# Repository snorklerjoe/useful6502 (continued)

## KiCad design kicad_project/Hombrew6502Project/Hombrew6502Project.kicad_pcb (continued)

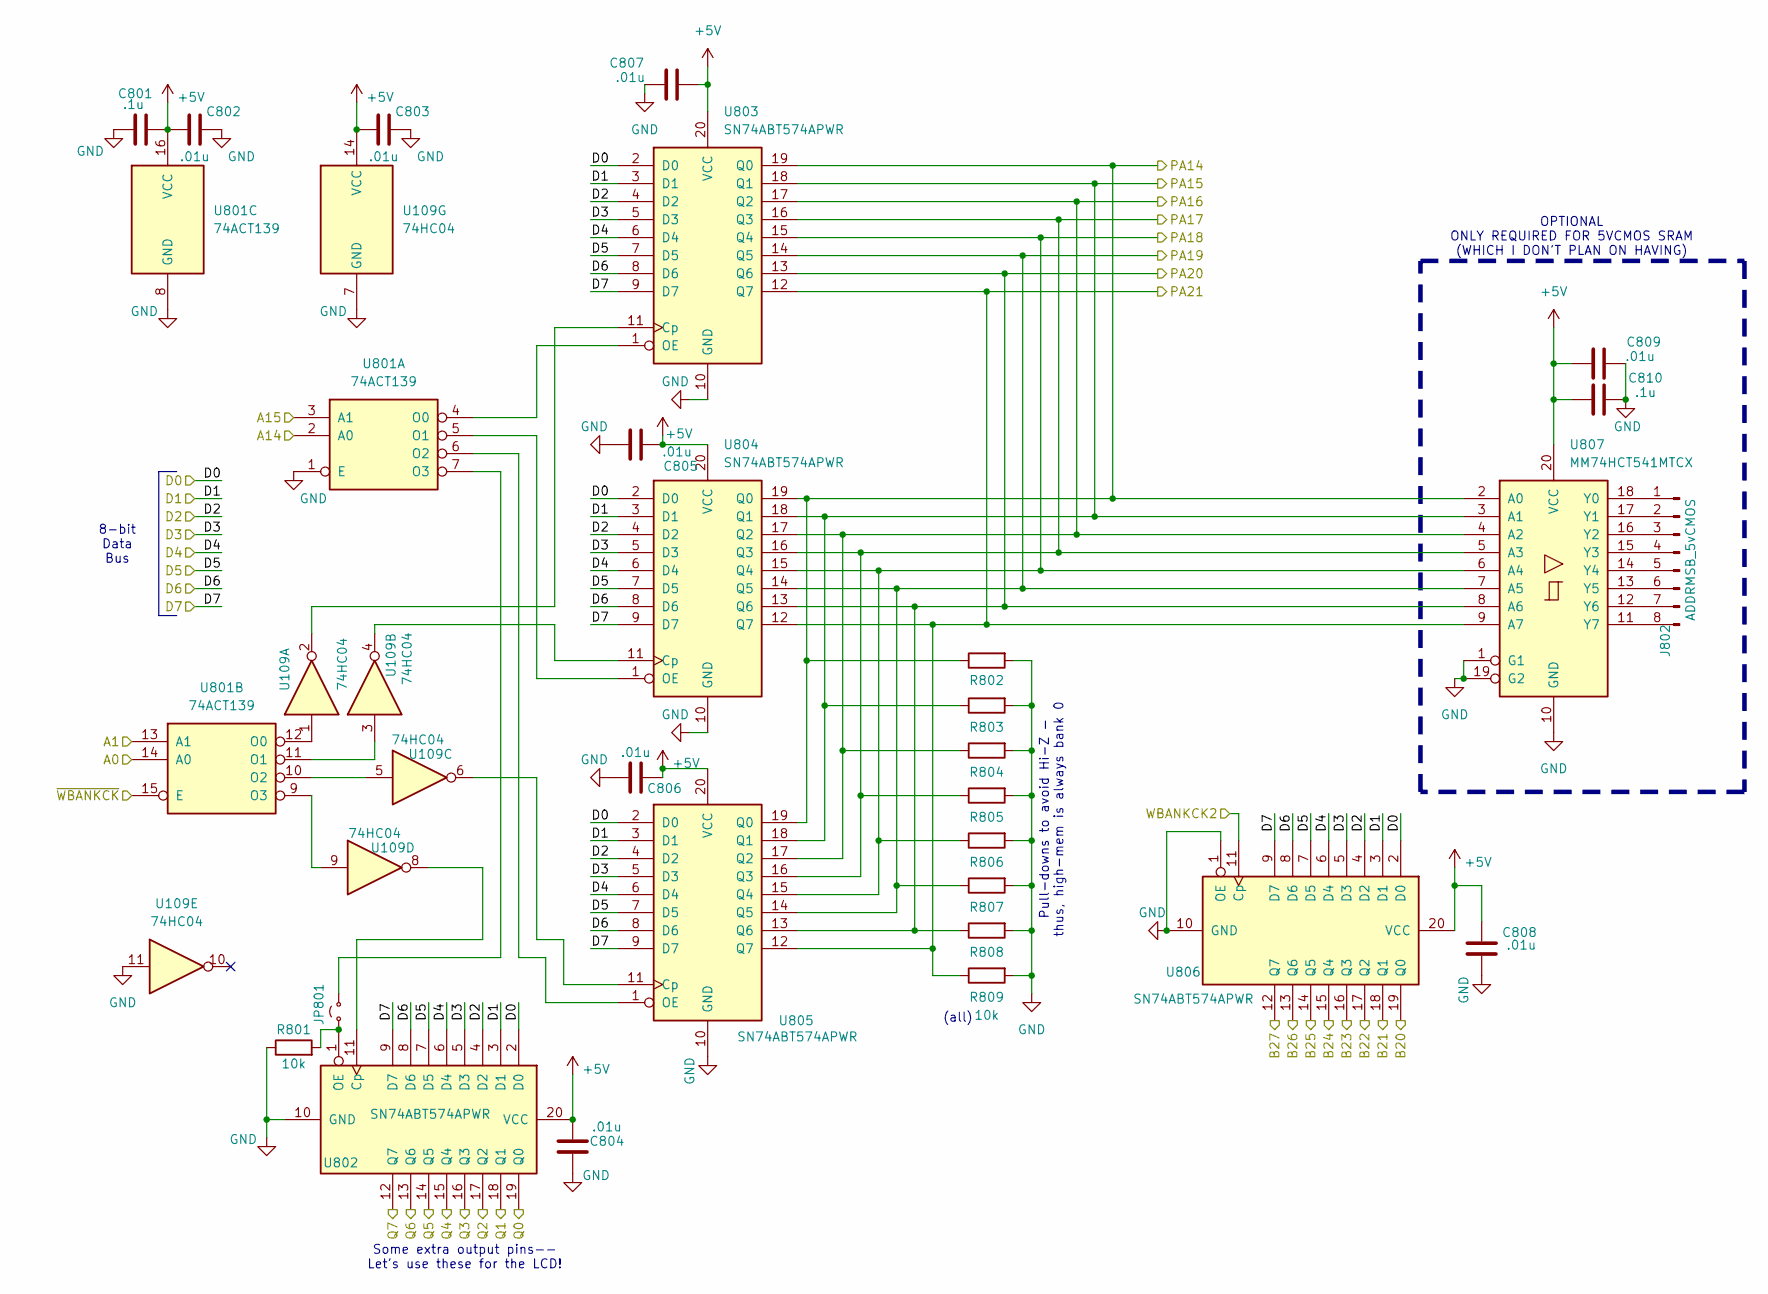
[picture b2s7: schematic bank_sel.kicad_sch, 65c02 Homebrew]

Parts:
C801: .1u; C_0402_1005Metric
C802, C803, C804, C805, C806, C807, C808: .01u; C_0402_1005Metric
C809: .01u
C810: .1u
J802: ADDRMSB_5vCMOS
JP801: Jumper_2_Small_Open; SolderJumper-2_P1.3mm_Open_Pad1.0x1.5mm
R801, R802, R803, R804, R805, R806, R807, R808, R809: 10k; R_0402_1005Metric
U109: 74HC04; SOIC-14_3.9x8.7mm_P1.27mm
U801: 74ACT139; TSSOP-16_4.4x5mm_P0.65mm
U802, U803, U804, U805, U806: SN74ABT574APWR; TSSOP-20_4.4x6.5mm_P0.65mm
U807: MM74HCT541MTCX

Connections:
+5V: C801.2, C802.1, C803.1, C804.2, C805.2, C806.2, C807.1, C808.2, C809.1, C810.1, U109.14 (VCC), U801.16 (VCC), U802.20 (VCC), U803.20 (VCC), U804.20 (VCC), U805.20 (VCC), U806.20 (VCC), U807.20 (VCC); also elsewhere on the board
/A0: U801.14 (A0); also elsewhere on the board
/A1: U801.13 (A1); also elsewhere on the board
/A14: U801.2 (A0); also elsewhere on the board
/A15: U801.3 (A1); also elsewhere on the board
/Bank Selection/WBANKCK2: U806.11 (Cp); also elsewhere on the board
/Bank Selection/~WBANKCK: U801.15 (E); also elsewhere on the board
/D0: U802.2 (D0), U803.2 (D0), U804.2 (D0), U805.2 (D0), U806.2 (D0); also elsewhere on the board
/D1: U802.3 (D1), U803.3 (D1), U804.3 (D1), U805.3 (D1), U806.3 (D1); also elsewhere on the board
/D2: U802.4 (D2), U803.4 (D2), U804.4 (D2), U805.4 (D2), U806.4 (D2); also elsewhere on the board
/D3: U802.5 (D3), U803.5 (D3), U804.5 (D3), U805.5 (D3), U806.5 (D3); also elsewhere on the board
/D4: U802.6 (D4), U803.6 (D4), U804.6 (D4), U805.6 (D4), U806.6 (D4); also elsewhere on the board
/D5: U802.7 (D5), U803.7 (D5), U804.7 (D5), U805.7 (D5), U806.7 (D5); also elsewhere on the board
/D6: U802.8 (D6), U803.8 (D6), U804.8 (D6), U805.8 (D6), U806.8 (D6); also elsewhere on the board
/D7: U802.9 (D7), U803.9 (D7), U804.9 (D7), U805.9 (D7), U806.9 (D7); also elsewhere on the board
/PQ0: U802.19 (Q0); also elsewhere on the board
/PQ1: U802.18 (Q1); also elsewhere on the board
/PQ2: U802.17 (Q2); also elsewhere on the board
/PQ3: U802.16 (Q3); also elsewhere on the board
/PQ4: U802.15 (Q4); also elsewhere on the board
/PQ5: U802.14 (Q5); also elsewhere on the board
/PQ6: U802.13 (Q6); also elsewhere on the board
/PQ7: U802.12 (Q7); also elsewhere on the board
/SRAM Banks/B20: U806.19 (Q0); also elsewhere on the board
/SRAM Banks/B21: U806.18 (Q1); also elsewhere on the board
/SRAM Banks/B22: U806.17 (Q2); also elsewhere on the board
/SRAM Banks/B23: U806.16 (Q3); also elsewhere on the board
/SRAM Banks/B24: U806.15 (Q4); also elsewhere on the board
/SRAM Banks/B25: U806.14 (Q5); also elsewhere on the board
/SRAM Banks/B26: U806.13 (Q6); also elsewhere on the board
/SRAM Banks/B27: U806.12 (Q7); also elsewhere on the board
/SRAM Banks/PA14: R802.1, U803.19 (Q0), U804.19 (Q0), U805.19 (Q0), U807.2 (A0); also elsewhere on the board
/SRAM Banks/PA15: R803.1, U803.18 (Q1), U804.18 (Q1), U805.18 (Q1), U807.3 (A1); also elsewhere on the board
/SRAM Banks/PA16: R804.1, U803.17 (Q2), U804.17 (Q2), U805.17 (Q2), U807.4 (A2); also elsewhere on the board
/SRAM Banks/PA17: R805.1, U803.16 (Q3), U804.16 (Q3), U805.16 (Q3), U807.5 (A3); also elsewhere on the board
/SRAM Banks/PA18: R806.1, U803.15 (Q4), U804.15 (Q4), U805.15 (Q4), U807.6 (A4); also elsewhere on the board
/SRAM Banks/PA19: R807.1, U803.14 (Q5), U804.14 (Q5), U805.14 (Q5), U807.7 (A5); also elsewhere on the board
/SRAM Banks/PA20: R808.1, U803.13 (Q6), U804.13 (Q6), U805.13 (Q6), U807.8 (A6); also elsewhere on the board
/SRAM Banks/PA21: R809.1, U803.12 (Q7), U804.12 (Q7), U805.12 (Q7), U807.9 (A7); also elsewhere on the board
GND: C801.1, C802.2, C803.2, C804.1, C805.1, C806.1, C807.2, C808.1, C809.2, C810.2, R801.1, R802.2, R803.2, R804.2, R805.2, R806.2, R807.2, R808.2, R809.2, U109.7 (GND), U109.11, U801.1 (E), U801.8 (GND), U802.10 (GND), U803.10 (GND), U804.10 (GND), U805.10 (GND), U806.1 (OE), U806.10 (GND), U807.1 (G1), U807.10 (GND), U807.19 (G2); also elsewhere on the board
unnamed: J802.1, U807.18 (Y0)
unnamed: J802.2, U807.17 (Y1)
unnamed: J802.3, U807.16 (Y2)
unnamed: J802.4, U807.15 (Y3)
unnamed: J802.5, U807.14 (Y4)
unnamed: J802.6, U807.13 (Y5)
unnamed: J802.7, U807.12 (Y6)
unnamed: J802.8, U807.11 (Y7)
unnamed: JP801.1 (A), R801.2, U802.1 (OE)
unnamed: JP801.2 (B), U801.7 (O3)
unnamed: U801.4 (O0), U803.1 (OE)
unnamed: U801.5 (O1), U804.1 (OE)
unnamed: U801.6 (O2), U805.1 (OE)
unnamed: U109.1, U801.12 (O0)
unnamed: U109.3, U801.11 (O1)
unnamed: U109.5, U801.10 (O2)
unnamed: U109.9, U801.9 (O3)
unnamed: U109.8, U802.11 (Cp)
unnamed: U109.2, U803.11 (Cp)
unnamed: U109.4, U804.11 (Cp)
unnamed: U109.6, U805.11 (Cp)

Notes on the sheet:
Pull-downs to avoid Hi-Z — thus, high-mem is always bank 0
8-bit Data Bus
OPTIONAL ONLY REQUIRED FOR 5VCMOS SRAM (WHICH I DON'T PLAN ON HAVING)
Some extra output pins-- Let's use these for the LCD!
(all)

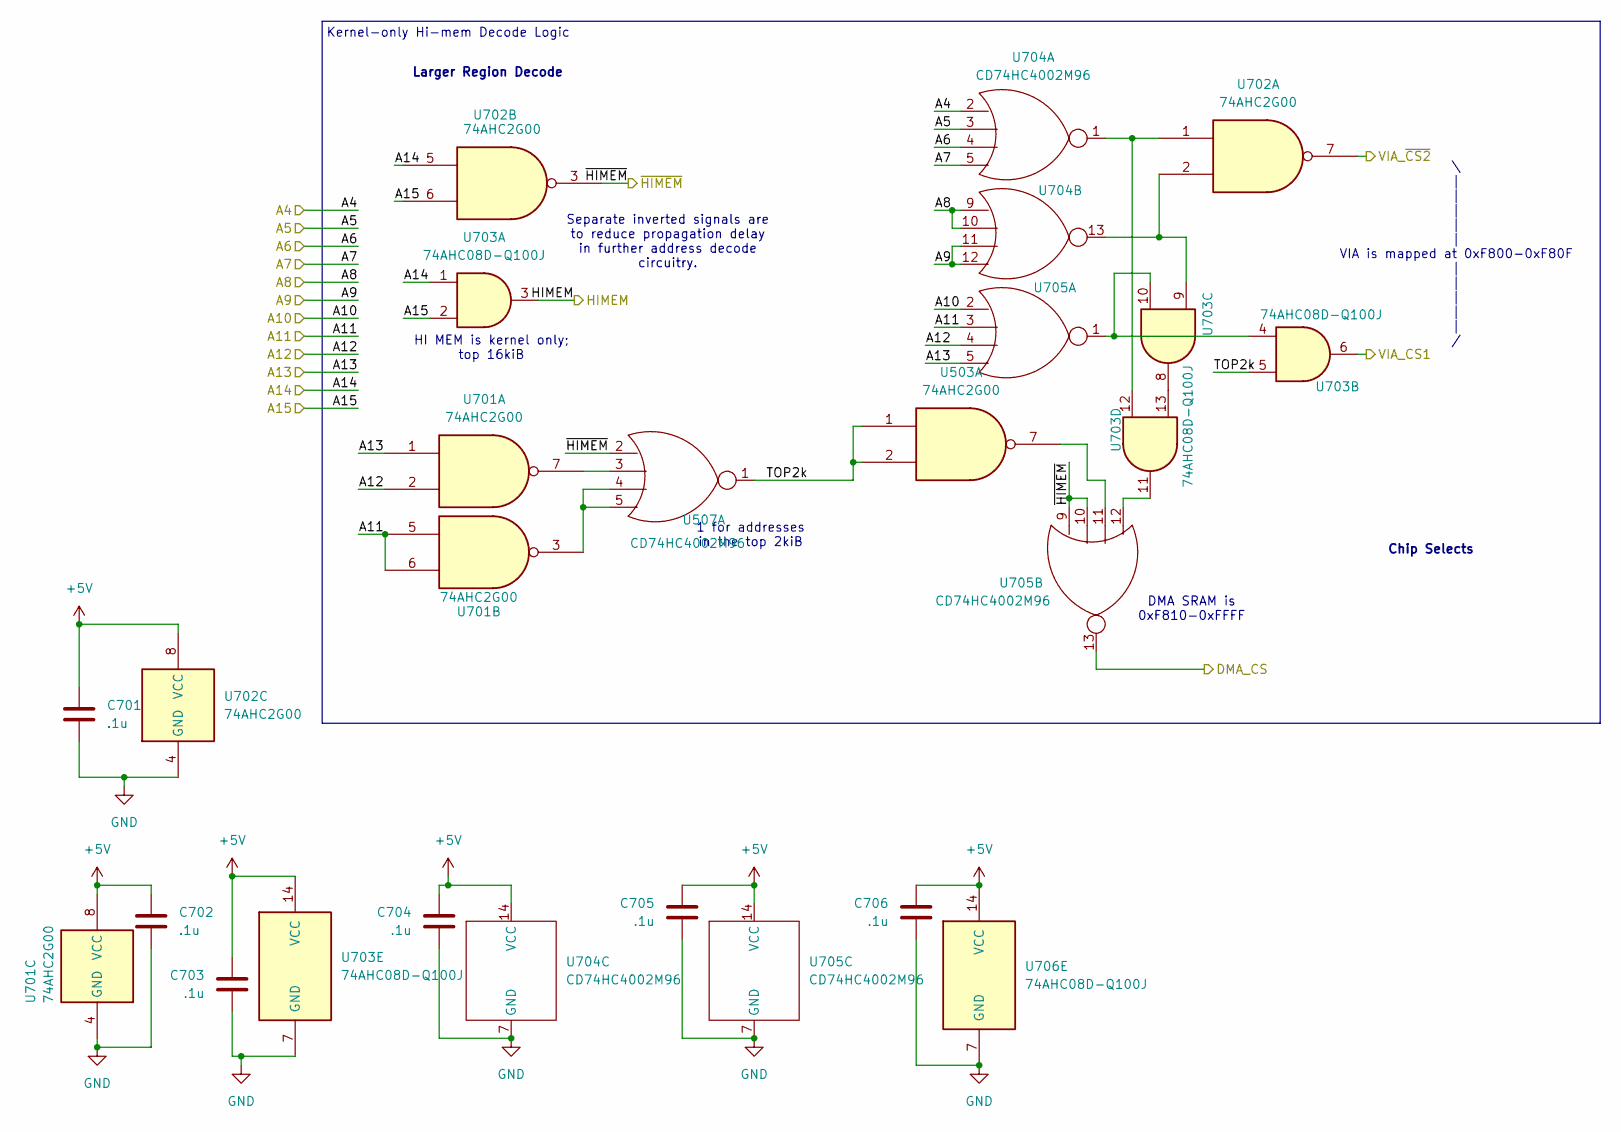
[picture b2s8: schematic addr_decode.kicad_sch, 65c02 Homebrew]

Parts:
C701, C702, C703, C704, C705, C706: .1u; C_0402_1005Metric
U503, U701, U702: 74AHC2G00; TSSOP-8_3x3mm_P0.65mm
U507, U704, U705: CD74HC4002M96; SOIC-14_3.9x8.7mm_P1.27mm
U703, U706: 74AHC08D-Q100J; SOIC-14_3.9x8.7mm_P1.27mm

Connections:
+5V: C701.1, C702.1, C703.1, C704.1, C705.1, C706.1, U701.8 (VCC), U702.8 (VCC), U703.14 (VCC), U704.14 (VCC), U705.14 (VCC), U706.14 (VCC); also elsewhere on the board
/A4: U704.2; also elsewhere on the board
/A5: U704.3; also elsewhere on the board
/A6: U704.4; also elsewhere on the board
/A7: U704.5; also elsewhere on the board
/A8: U704.9, U704.10; also elsewhere on the board
/A9: U704.11, U704.12; also elsewhere on the board
/A10: U705.2; also elsewhere on the board
/A11: U701.5, U701.6, U705.3; also elsewhere on the board
/A12: U701.2, U705.4; also elsewhere on the board
/A13: U701.1, U705.5; also elsewhere on the board
/A14: U702.5, U703.1; also elsewhere on the board
/A15: U702.6, U703.2; also elsewhere on the board
/HIMEM: U703.3; also elsewhere on the board
/High-Memory Address Decode/TOP2k: U503.1, U503.2, U507.1, U703.5
/VIA_CS1: U703.6; also elsewhere on the board
/VIA_~CS2: U702.7; also elsewhere on the board
/~DMA_CS: U705.13; also elsewhere on the board
/~HIMEM: U507.2, U702.3, U705.9, U705.10; also elsewhere on the board
GND: C701.2, C702.2, C703.2, C704.2, C705.2, C706.2, U701.4 (GND), U702.4 (GND), U703.7 (GND), U704.7 (GND), U705.7 (GND), U706.7 (GND); also elsewhere on the board
unnamed: U503.7, U705.11
unnamed: U507.3, U701.7
unnamed: U507.4, U507.5, U701.3
unnamed: U702.1, U703.12, U704.1
unnamed: U702.2, U703.9, U704.13
unnamed: U703.4, U703.10, U705.1
unnamed: U703.11, U705.12
unnamed: U703.8, U703.13

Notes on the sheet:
Larger Region Decode
Separate inverted signals are to reduce propagation delay in further address decode circuitry.
HI MEM is kernel only; top 16kiB
Chip Selects
Kernel-only Hi-mem Decode Logic
\ | | | | | VIA is mapped at 0xF800-0xF80F | | | | | /
1 for addresses in the top 2kiB
DMA SRAM is 0xF810-0xFFFF

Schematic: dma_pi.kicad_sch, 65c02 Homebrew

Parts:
C201: 4.7u; C_0402_1005Metric
C202, C209, C213, C216, C217: .01u; C_0402_1005Metric
C203, C204: NOPOP; C_0402_1005Metric
C205: .01u; C_0402_1005Metric; not fitted
C206, C211: 0.1u; C_0402_1005Metric
C207, C210, C212, C214: 1u; C_0402_1005Metric
C208, C215, C218: .1u; C_0402_1005Metric
J201: ICSP Header; PinHeader_1x06_P2.54mm_Vertical
J202, J203, J205, J206: Conn_02x05_Odd_Even; PinHeader_2x05_P2.54mm_Vertical_SMD
J204: I2C; PinHeader_1x05_P2.54mm_Vertical
J210: UART; FanPinHeader_1x03_P2.54mm_Vertical
JP201: Jumper_2_Small_Bridged; SolderJumper-2_P1.3mm_Bridged2Bar_Pad1.0x1.5mm
JP202: Jumper_2_Small_Open; SolderJumper-2_P1.3mm_Open_Pad1.0x1.5mm
JP203: ICSP modeset; SolderJumper-2_P1.3mm_Bridged2Bar_Pad1.0x1.5mm
JP204: BS_CTRL; SolderJumper-2_P1.3mm_Open_Pad1.0x1.5mm
JP205: BS_CTRL2; SolderJumper-2_P1.3mm_Bridged2Bar_Pad1.0x1.5mm
JP206: OE_CTRL; SolderJumper-2_P1.3mm_Bridged2Bar_Pad1.0x1.5mm
JP207: RW_CTRL; SolderJumper-2_P1.3mm_Bridged2Bar_Pad1.0x1.5mm
JP208: CE_CTRL; SolderJumper-2_P1.3mm_Open_Pad1.0x1.5mm
JP209: UART pin sel; SolderJumper-3_P1.3mm_Bridged12_Pad1.0x1.5mm
R201: NOPOP; R_0402_1005Metric
R202, R203: NOPOP; R_0402_1005Metric; not fitted
R204, R215, R219, R220, R221: 4.7k; R_0402_1005Metric
R205, R206, R207, R208, R209, R210, R211, R212: 33; R_0402_1005Metric
R213, R214, R218: 100; R_0402_1005Metric
R216, R217: 10k; R_0402_1005Metric
TP201: INT; TestPoint_Pad_D1.5mm
U201: SN74LS07; SOIC-14_3.9x8.7mm_P1.27mm
U202: CY7C146-25JC; 845221B1RKTP
U203: PIC16F15385-xPT; TQFP-48_7x7mm_P0.5mm
Y201: NOPOP; Crystal_SMD_2016-4Pin_2.0x1.6mm

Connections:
+3V3: J203.6, J204.1, J205.6; also elsewhere on the board
+5V: C201.1, C202.2, C205.2, C206.1, C207.1, C208.1, C209.1, C210.1, C211.1, C212.1, C214.1, C215.1, C216.1, C217.1, C218.1, J201.2, J202.3, J203.4, J204.2, J205.4, J206.10, R202.2, R203.2, R216.1, R217.1, U201.14 (VCC), U202.52 (VCC), U203.7 (VDD), U203.30 (VDD); also elsewhere on the board
/A0: U202.7 (A0_L); also elsewhere on the board
/A1: U202.8 (A1_L); also elsewhere on the board
/A2: U202.9 (A2_L); also elsewhere on the board
/A3: U202.10 (A3_L); also elsewhere on the board
/A4: U202.11 (A4_L); also elsewhere on the board
/A5: U202.12 (A5_L); also elsewhere on the board
/A6: U202.13 (A6_L); also elsewhere on the board
/A7: U202.14 (A7_L); also elsewhere on the board
/A8: U202.15 (A8_L); also elsewhere on the board
/A9: U202.16 (A9_L); also elsewhere on the board
/A10: U202.5 (A10_L); also elsewhere on the board
/DMA Peripheral Interface/6502_D0: R205.1; also elsewhere on the board
/DMA Peripheral Interface/6502_D1: R206.1; also elsewhere on the board
/DMA Peripheral Interface/6502_D2: R207.1; also elsewhere on the board
/DMA Peripheral Interface/6502_D3: R208.1; also elsewhere on the board
/DMA Peripheral Interface/6502_D4: R209.1; also elsewhere on the board
/DMA Peripheral Interface/6502_D5: R210.1; also elsewhere on the board
/DMA Peripheral Interface/6502_D6: R211.1; also elsewhere on the board
/DMA Peripheral Interface/6502_D7: R212.1; also elsewhere on the board
/DMA Peripheral Interface/DMA Peripheral Interface Module/AUX_INT1: J206.6, U201.3
/DMA Peripheral Interface/DMA Peripheral Interface Module/AUX_SEL: J202.10, J206.4, JP204.2 (B), U203.2 (RD4)
/DMA Peripheral Interface/DMA Peripheral Interface Module/CLKIN: C204.1, U203.32 (RA7), Y201.1
/DMA Peripheral Interface/DMA Peripheral Interface Module/CLKOUT: R201.1, U203.33 (RA6)
/DMA Peripheral Interface/DMA Peripheral Interface Module/DMA_A0: U202.45 (A0_R), U203.34 (RC0)
/DMA Peripheral Interface/DMA Peripheral Interface Module/DMA_A1: U202.44 (A1_R), U203.35 (RC1)
/DMA Peripheral Interface/DMA Peripheral Interface Module/DMA_A2: U202.43 (A2_R), U203.40 (RC2)
/DMA Peripheral Interface/DMA Peripheral Interface Module/DMA_A3: U202.42 (A3_R), U203.41 (RC3)
/DMA Peripheral Interface/DMA Peripheral Interface Module/DMA_A4: U202.41 (A4_R), U203.46 (RC4)
/DMA Peripheral Interface/DMA Peripheral Interface Module/DMA_A5: U202.40 (A5_R), U203.47 (RC5)
/DMA Peripheral Interface/DMA Peripheral Interface Module/DMA_A6: U202.39 (A6_R), U203.48 (RC6)
/DMA Peripheral Interface/DMA Peripheral Interface Module/DMA_A7: U202.38 (A7_R), U203.1 (RC7)
/DMA Peripheral Interface/DMA Peripheral Interface Module/DMA_A8: U202.37 (A8_R), U203.29 (RE2)
/DMA Peripheral Interface/DMA Peripheral Interface Module/DMA_A9: U202.36 (A9_R), U203.28 (RE1)
/DMA Peripheral Interface/DMA Peripheral Interface Module/DMA_A10: U202.47 (A10_R), U203.27 (RE0)
/DMA Peripheral Interface/DMA Peripheral Interface Module/DMA_BS: JP204.1 (A), JP205.1 (A), U202.49 (BUSY_R)
/DMA Peripheral Interface/DMA Peripheral Interface Module/DMA_CE: JP208.2 (B), R215.2, U202.51 (CE_R)
/DMA Peripheral Interface/DMA Peripheral Interface Module/DMA_D0: U202.27 (D0_R), U203.36 (RF0)
/DMA Peripheral Interface/DMA Peripheral Interface Module/DMA_D1: U202.28 (D1_R), U203.37 (RF1)
/DMA Peripheral Interface/DMA Peripheral Interface Module/DMA_D2: U202.29 (D2_R), U203.38 (RF2)
/DMA Peripheral Interface/DMA Peripheral Interface Module/DMA_D3: U202.30 (D3_R), U203.39 (RF3)
/DMA Peripheral Interface/DMA Peripheral Interface Module/DMA_D4: U202.31 (D4_R), U203.12 (RF4)
/DMA Peripheral Interface/DMA Peripheral Interface Module/DMA_D5: U202.32 (D5_R), U203.13 (RF5)
/DMA Peripheral Interface/DMA Peripheral Interface Module/DMA_D6: U202.33 (D6_R), U203.14 (RF6)
/DMA Peripheral Interface/DMA Peripheral Interface Module/DMA_D7: U202.34 (D7_R), U203.15 (RF7)
/DMA Peripheral Interface/DMA Peripheral Interface Module/DMA_INT: R216.2, U202.48 (INT_R)
/DMA Peripheral Interface/DMA Peripheral Interface Module/DMA_OE: JP206.2 (B), U202.46 (OE_R)
/DMA Peripheral Interface/DMA Peripheral Interface Module/DMA_RW: JP207.2 (B), U202.50 (RW_R)
/DMA Peripheral Interface/DMA Peripheral Interface Module/PIC Peripherals/OC_MO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: U201.10; also elsewhere on the board
/DMA Peripheral Interface/DMA Peripheral Interface Module/PIC Peripherals/OC_SCK: U201.12; also elsewhere on the board
/DMA Peripheral Interface/DMA Peripheral Interface Module/PIC Peripherals/OC_SS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: U201.8; also elsewhere on the board
/DMA Peripheral Interface/DMA Peripheral Interface Module/PIC_INT: U201.2, U201.4, U203.26 (RA5)
/DMA Peripheral Interface/DMA Peripheral Interface Module/SS_AUX: J206.9, U203.23 (RA2)
/DMA Peripheral Interface/DMA Peripheral Interface Module/SS_MEM: U203.25 (RA4); also elsewhere on the board
/DMA Peripheral Interface/DMA Peripheral Interface Module/SS_SD: U201.9, U203.24 (RA3)
/DMA Peripheral Interface/DMA Peripheral Interface Module/UARTrx: J203.9, J205.9, J210.2, R220.2
/DMA Peripheral Interface/DMA Peripheral Interface Module/UARTtx: J203.7, J205.7, J210.3, R219.1
/DMA Peripheral Interface/~BUSY: U202.3 (BUSY_L); also elsewhere on the board
/IO_CMD: U201.1; also elsewhere on the board
/R~W: U202.2 (RW_L); also elsewhere on the board
/~DMA_CS: JP201.2 (B), JP202.1 (A); also elsewhere on the board
/~IRQ: U203.21 (RA0); also elsewhere on the board
GND: C201.2, C202.1, C203.1, C204.2, C205.1, C206.2, C207.2, C208.2, C209.2, C210.2, C211.2, C212.2, C213.2, C214.2, C215.2, C216.2, C217.2, C218.2, J201.3, J202.1, J203.2, J203.5, J203.8, J203.10, J204.5, J205.2, J205.5, J205.8, J205.10, J206.2, J206.7, J206.8, J210.1, R204.2, R215.1, R221.2, U201.7 (GND), U202.26 (GND), U203.6 (VSS), U203.31 (VSS), Y201.2, Y201.4; also elsewhere on the board
ICSPCLK: JP209.3 (B), R214.1, U203.18 (ICSPCLK/RB6)
ICSPDAT: JP209.1 (A), R213.1, U203.19 (ICSPDAT/RB7)
ICSPMCLR: J201.1, JP203.2 (B), R217.2, R218.1
MISO: J206.5, U203.9 (RB1); also elsewhere on the board
MOSI: J206.3, U201.11, U203.10 (RB2); also elsewhere on the board
unnamed: C203.2, R201.2, Y201.3
unnamed: J201.4, R213.2
unnamed: J201.5, R214.2
unnamed: J202.2, U203.42 (RD0)
unnamed: J202.4, U203.43 (RD1)
unnamed: J202.5, JP206.1 (A), U203.5 (RD7)
unnamed: J202.6, U203.44 (RD2)
unnamed: J202.7, JP207.1 (A), U203.4 (RD6)
unnamed: J202.8, U203.45 (RD3)
unnamed: J202.9, JP205.2 (B), JP208.1 (A), U203.3 (RD5)
unnamed: JP201.1 (A), U202.6 (OE_L)
unnamed: JP202.2 (B), R204.1, U202.1 (CE_L)
unnamed: C213.1, JP203.1 (A)
unnamed: JP209.2 (C), R220.1
unnamed: R205.2, U202.17 (D0_L)
unnamed: R206.2, U202.18 (D1_L)
unnamed: R207.2, U202.19 (D2_L)
unnamed: R208.2, U202.20 (D3_L)
unnamed: R209.2, U202.21 (D4_L)
unnamed: R210.2, U202.22 (D5_L)
unnamed: R211.2, U202.23 (D6_L)
unnamed: R212.2, U202.24 (D7_L)
unnamed: TP201.1, U202.4 (INT_L)
unnamed: R221.1, U201.5, U203.22 (RA1)
unnamed: R219.2, U203.17 (RB5)
unnamed: R218.2, U203.20 (VPP/~MCLR/RE3)
RESB: U201.6; also elsewhere on the board
SCK: J206.1, U201.13, U203.8 (RB0); also elsewhere on the board
SCL: J203.3, J204.4, J205.3, R203.1, U203.11 (RB3)
SDA: J203.1, J204.3, J205.1, R202.1, U203.16 (RB4)

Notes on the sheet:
Peripherals
PIC AUX Interfaces
SPI Slave Select
Interrupt line to 6502 for DMA data ready (CMOS compatible)
DMA Interrupt Lines (Active Low)
(for ext. crystal)
(PIC16 Peripheral Interface Coprocessor)
Optional external i2c pull-ups These can be internal to the PIC. Otherwise, these should both be ≥4.7k
Optional PIC Interfaces
Provision for an external ESP-01 Interface
Optional external crystal; enable in software if provided
Interrupt line to PIC for DMA data ready (CMOS-compatible)
Dual-port RAM is used as hardware-shared memory between 6502 & PIC
ICSP & UART
SPI Master
To reset the CPU
I2C Master
Resistors in case of accidentally reversing tx & rx

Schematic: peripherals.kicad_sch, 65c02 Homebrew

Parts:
C401, C403: 1u; C_0402_1005Metric
C402, C404: .1u; C_0402_1005Metric
C405: .01u; C_0402_1005Metric
D401: LED; LED_0402_1005Metric
J402: Micro_SD_Card; microSD_HC_Wuerth_693072010801
J403: Conn_02x03_Odd_Even; PinHeader_2x03_P2.54mm_Vertical_SMD
R401, R402, R403, R404: 10k; R_0402_1005Metric
R405: 470; R_0402_1005Metric
U401: 74HCT125D; SOIC-14_3.9x8.7mm_P1.27mm
U402: M95512-Axxx-MF; TSSOP-8_4.4x3mm_P0.65mm

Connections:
+3V3: C403.1, C404.1, J402.4 (VDD), J403.5, R401.1, R402.1, R403.1, R404.1, R405.2; also elsewhere on the board
+5V: C401.1, C402.1, C405.1, U401.14 (Vcc), U402.3 (~W), U402.7 (~HOLD), U402.8 (VCC); also elsewhere on the board
/DMA Peripheral Interface/DMA Peripheral Interface Module/PIC Peripherals/OC_MO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: J402.3 (CMD), J403.3, R402.2; also elsewhere on the board
/DMA Peripheral Interface/DMA Peripheral Interface Module/PIC Peripherals/OC_SCK: J402.5 (CLK), J403.6, R403.2; also elsewhere on the board
/DMA Peripheral Interface/DMA Peripheral Interface Module/PIC Peripherals/OC_SS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: D401.1 (K), J402.2 (DAT3/CD), J403.1, R404.2, U401.1 (~OE); also elsewhere on the board
/DMA Peripheral Interface/DMA Peripheral Interface Module/PIC Peripherals/SD_MI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: J402.7 (DAT0), J403.2, R401.2, U401.2 (A)
/DMA Peripheral Interface/DMA Peripheral Interface Module/SS_MEM: U402.1 (~S); also elsewhere on the board
GND: C401.2, C402.2, C403.2, C404.2, C405.2, J402.6 (VSS), J402.9 (SHIELD), J403.4, U401.4 (~OE), U401.5 (A), U401.7 (GND), U401.9 (A), U401.10 (~OE), U401.12 (A), U401.13 (~OE), U402.4 (VSS); also elsewhere on the board
MISO: U401.3 (Y), U402.2 (Q); also elsewhere on the board
MOSI: U402.5 (D); also elsewhere on the board
unnamed: D401.2 (A), R405.1
SCK: U402.6 (C); also elsewhere on the board

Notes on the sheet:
3.3v CMOS (5V TTL-compatible)
Interface from DMA Schematic
Unused Components
EEPROM Slave Select
SD Card Hardware
\ | SPI | /
Pull-ups for open- collector
SPI EEPROM (for 6502 boot image)
Tri-state 5V CMOS
Optional, Provisionary Interfaces
Open-collector SD SPI signals
SD Card BUSY

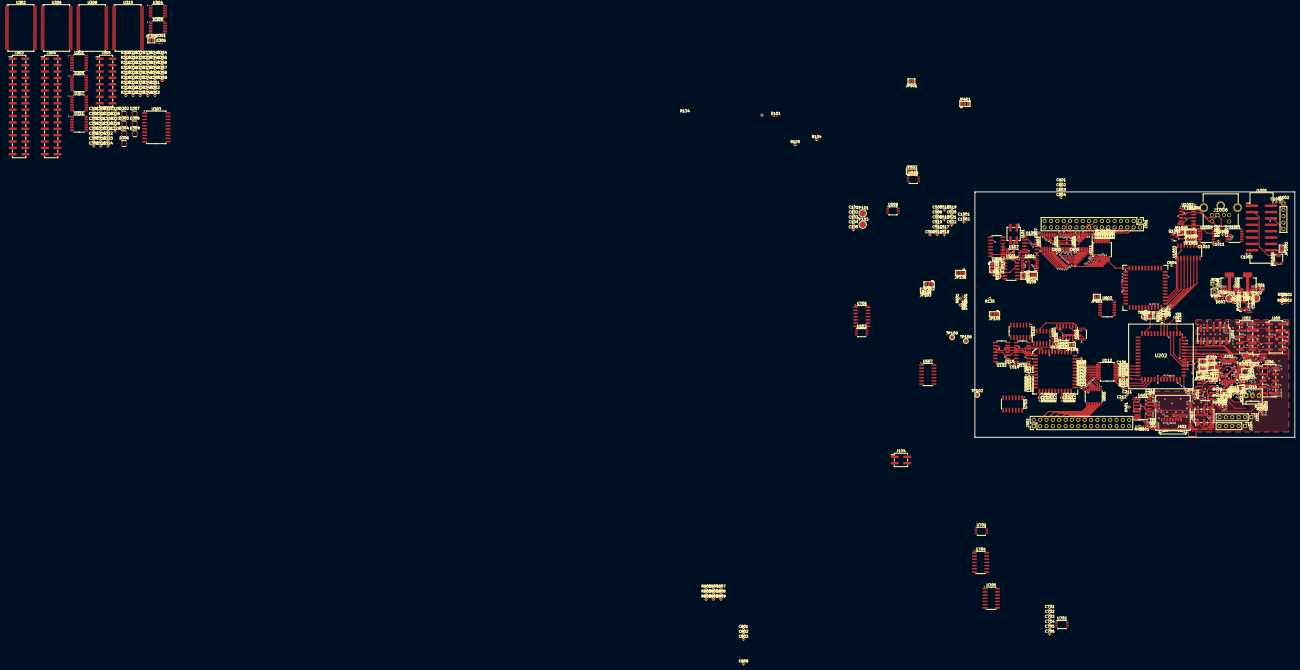
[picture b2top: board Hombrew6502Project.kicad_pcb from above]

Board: 4 copper layers, 127.6 x 98.0 mm, 378 parts (0 on the bottom side), 408 nets.

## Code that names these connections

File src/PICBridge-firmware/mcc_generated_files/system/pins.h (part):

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// get/set IO_RA5 aliases
#define IO_RA5_TRIS                 TRISAbits.TRISA5
#define IO_RA5_LAT                  LATAbits.LATA5
#define IO_RA5_PORT                 PORTAbits.RA5
#define IO_RA5_WPU                  WPUAbits.WPUA5
#define IO_RA5_OD                   ODCONAbits.ODCA5
#define IO_RA5_ANS                  ANSELAbits.ANSA5
#define IO_RA5_SetHigh()            do { LATAbits.LATA5 = 1; } while(0)
#define IO_RA5_SetLow()             do { LATAbits.LATA5 = 0; } while(0)
#define IO_RA5_Toggle()             do { LATAbits.LATA5 = ~LATAbits.LATA5; } while(0)
#define IO_RA5_GetValue()           PORTAbits.RA5
#define IO_RA5_SetDigitalInput()    do { TRISAbits.TRISA5 = 1; } while(0)
#define IO_RA5_SetDigitalOutput()   do { TRISAbits.TRISA5 = 0; } while(0)
#define IO_RA5_SetPullup()          do { WPUAbits.WPUA5 = 1; } while(0)
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// get/set IO_RB0 aliases
#define IO_RB0_TRIS                 TRISBbits.TRISB0
#define IO_RB0_LAT                  LATBbits.LATB0
#define IO_RB0_PORT                 PORTBbits.RB0
#define IO_RB0_WPU                  WPUBbits.WPUB0
#define IO_RB0_OD                   ODCONBbits.ODCB0
#define IO_RB0_ANS                  ANSELBbits.ANSB0
#define IO_RB0_SetHigh()            do { LATBbits.LATB0 = 1; } while(0)
#define IO_RB0_SetLow()             do { LATBbits.LATB0 = 0; } while(0)
#define IO_RB0_Toggle()             do { LATBbits.LATB0 = ~LATBbits.LATB0; } while(0)
#define IO_RB0_GetValue()           PORTBbits.RB0
#define IO_RB0_SetDigitalInput()    do { TRISBbits.TRISB0 = 1; } while(0)
#define IO_RB0_SetDigitalOutput()   do { TRISBbits.TRISB0 = 0; } while(0)
#define IO_RB0_SetPullup()          do { WPUBbits.WPUB0 = 1; } while(0)
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// get/set IO_RB1 aliases
#define IO_RB1_TRIS                 TRISBbits.TRISB1
#define IO_RB1_LAT                  LATBbits.LATB1
#define IO_RB1_PORT                 PORTBbits.RB1
#define IO_RB1_WPU                  WPUBbits.WPUB1
#define IO_RB1_OD                   ODCONBbits.ODCB1
#define IO_RB1_ANS                  ANSELBbits.ANSB1
#define IO_RB1_SetHigh()            do { LATBbits.LATB1 = 1; } while(0)
#define IO_RB1_SetLow()             do { LATBbits.LATB1 = 0; } while(0)
#define IO_RB1_Toggle()             do { LATBbits.LATB1 = ~LATBbits.LATB1; } while(0)
#define IO_RB1_GetValue()           PORTBbits.RB1
#define IO_RB1_SetDigitalInput()    do { TRISBbits.TRISB1 = 1; } while(0)
#define IO_RB1_SetDigitalOutput()   do { TRISBbits.TRISB1 = 0; } while(0)
#define IO_RB1_SetPullup()          do { WPUBbits.WPUB1 = 1; } while(0)
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// get/set IO_RB2 aliases
#define IO_RB2_TRIS                 TRISBbits.TRISB2
#define IO_RB2_LAT                  LATBbits.LATB2
#define IO_RB2_PORT                 PORTBbits.RB2
#define IO_RB2_WPU                  WPUBbits.WPUB2
#define IO_RB2_OD                   ODCONBbits.ODCB2
#define IO_RB2_ANS                  ANSELBbits.ANSB2
#define IO_RB2_SetHigh()            do { LATBbits.LATB2 = 1; } while(0)
#define IO_RB2_SetLow()             do { LATBbits.LATB2 = 0; } while(0)
#define IO_RB2_Toggle()             do { LATBbits.LATB2 = ~LATBbits.LATB2; } while(0)
#define IO_RB2_GetValue()           PORTBbits.RB2
#define IO_RB2_SetDigitalInput()    do { TRISBbits.TRISB2 = 1; } while(0)
#define IO_RB2_SetDigitalOutput()   do { TRISBbits.TRISB2 = 0; } while(0)
#define IO_RB2_SetPullup()          do { WPUBbits.WPUB2 = 1; } while(0)
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// get/set IO_RB3 aliases
#define IO_RB3_TRIS                 TRISBbits.TRISB3
#define IO_RB3_LAT                  LATBbits.LATB3
#define IO_RB3_PORT                 PORTBbits.RB3
#define IO_RB3_WPU                  WPUBbits.WPUB3
#define IO_RB3_OD                   ODCONBbits.ODCB3
#define IO_RB3_ANS                  ANSELBbits.ANSB3
#define IO_RB3_SetHigh()            do { LATBbits.LATB3 = 1; } while(0)
#define IO_RB3_SetLow()             do { LATBbits.LATB3 = 0; } while(0)
#define IO_RB3_Toggle()             do { LATBbits.LATB3 = ~LATBbits.LATB3; } while(0)
#define IO_RB3_GetValue()           PORTBbits.RB3
#define IO_RB3_SetDigitalInput()    do { TRISBbits.TRISB3 = 1; } while(0)
#define IO_RB3_SetDigitalOutput()   do { TRISBbits.TRISB3 = 0; } while(0)
#define IO_RB3_SetPullup()          do { WPUBbits.WPUB3 = 1; } while(0)
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// get/set IO_RB4 aliases
#define IO_RB4_TRIS                 TRISBbits.TRISB4
#define IO_RB4_LAT                  LATBbits.LATB4
#define IO_RB4_PORT                 PORTBbits.RB4
#define IO_RB4_WPU                  WPUBbits.WPUB4
#define IO_RB4_OD                   ODCONBbits.ODCB4
#define IO_RB4_ANS                  ANSELBbits.ANSB4
#define IO_RB4_SetHigh()            do { LATBbits.LATB4 = 1; } while(0)
#define IO_RB4_SetLow()             do { LATBbits.LATB4 = 0; } while(0)
#define IO_RB4_Toggle()             do { LATBbits.LATB4 = ~LATBbits.LATB4; } while(0)
#define IO_RB4_GetValue()           PORTBbits.RB4
#define IO_RB4_SetDigitalInput()    do { TRISBbits.TRISB4 = 1; } while(0)
#define IO_RB4_SetDigitalOutput()   do { TRISBbits.TRISB4 = 0; } while(0)
#define IO_RB4_SetPullup()          do { WPUBbits.WPUB4 = 1; } while(0)
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// get/set IO_RB5 aliases
#define IO_RB5_TRIS                 TRISBbits.TRISB5
#define IO_RB5_LAT                  LATBbits.LATB5
#define IO_RB5_PORT                 PORTBbits.RB5
#define IO_RB5_WPU                  WPUBbits.WPUB5
#define IO_RB5_OD                   ODCONBbits.ODCB5
#define IO_RB5_ANS                  ANSELBbits.ANSB5
#define IO_RB5_SetHigh()            do { LATBbits.LATB5 = 1; } while(0)
#define IO_RB5_SetLow()             do { LATBbits.LATB5 = 0; } while(0)
#define IO_RB5_Toggle()             do { LATBbits.LATB5 = ~LATBbits.LATB5; } while(0)
#define IO_RB5_GetValue()           PORTBbits.RB5
#define IO_RB5_SetDigitalInput()    do { TRISBbits.TRISB5 = 1; } while(0)
#define IO_RB5_SetDigitalOutput()   do { TRISBbits.TRISB5 = 0; } while(0)
#define IO_RB5_SetPullup()          do { WPUBbits.WPUB5 = 1; } while(0)
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// get/set IO_RB7 aliases
#define IO_RB7_TRIS                 TRISBbits.TRISB7
#define IO_RB7_LAT                  LATBbits.LATB7
#define IO_RB7_PORT                 PORTBbits.RB7
#define IO_RB7_WPU                  WPUBbits.WPUB7
#define IO_RB7_OD                   ODCONBbits.ODCB7
#define IO_RB7_ANS                  ANSELBbits.ANSB7
#define IO_RB7_SetHigh()            do { LATBbits.LATB7 = 1; } while(0)
#define IO_RB7_SetLow()             do { LATBbits.LATB7 = 0; } while(0)
#define IO_RB7_Toggle()             do { LATBbits.LATB7 = ~LATBbits.LATB7; } while(0)
#define IO_RB7_GetValue()           PORTBbits.RB7
#define IO_RB7_SetDigitalInput()    do { TRISBbits.TRISB7 = 1; } while(0)
#define IO_RB7_SetDigitalOutput()   do { TRISBbits.TRISB7 = 0; } while(0)
#define IO_RB7_SetPullup()          do { WPUBbits.WPUB7 = 1; } while(0)
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// get/set IO_RC0 aliases
#define IO_RC0_TRIS                 TRISCbits.TRISC0
#define IO_RC0_LAT                  LATCbits.LATC0
#define IO_RC0_PORT                 PORTCbits.RC0
#define IO_RC0_WPU                  WPUCbits.WPUC0
#define IO_RC0_OD                   ODCONCbits.ODCC0
#define IO_RC0_ANS                  ANSELCbits.ANSC0
#define IO_RC0_SetHigh()            do { LATCbits.LATC0 = 1; } while(0)
#define IO_RC0_SetLow()             do { LATCbits.LATC0 = 0; } while(0)
#define IO_RC0_Toggle()             do { LATCbits.LATC0 = ~LATCbits.LATC0; } while(0)
#define IO_RC0_GetValue()           PORTCbits.RC0
#define IO_RC0_SetDigitalInput()    do { TRISCbits.TRISC0 = 1; } while(0)
#define IO_RC0_SetDigitalOutput()   do { TRISCbits.TRISC0 = 0; } while(0)
#define IO_RC0_SetPullup()          do { WPUCbits.WPUC0 = 1; } while(0)
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// get/set IO_RC1 aliases
#define IO_RC1_TRIS                 TRISCbits.TRISC1
#define IO_RC1_LAT                  LATCbits.LATC1
#define IO_RC1_PORT                 PORTCbits.RC1
#define IO_RC1_WPU                  WPUCbits.WPUC1
#define IO_RC1_OD                   ODCONCbits.ODCC1
#define IO_RC1_ANS                  ANSELCbits.ANSC1
#define IO_RC1_SetHigh()            do { LATCbits.LATC1 = 1; } while(0)
#define IO_RC1_SetLow()             do { LATCbits.LATC1 = 0; } while(0)
#define IO_RC1_Toggle()             do { LATCbits.LATC1 = ~LATCbits.LATC1; } while(0)
#define IO_RC1_GetValue()           PORTCbits.RC1
#define IO_RC1_SetDigitalInput()    do { TRISCbits.TRISC1 = 1; } while(0)
#define IO_RC1_SetDigitalOutput()   do { TRISCbits.TRISC1 = 0; } while(0)
#define IO_RC1_SetPullup()          do { WPUCbits.WPUC1 = 1; } while(0)
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// get/set IO_RC2 aliases
#define IO_RC2_TRIS                 TRISCbits.TRISC2
#define IO_RC2_LAT                  LATCbits.LATC2
#define IO_RC2_PORT                 PORTCbits.RC2
#define IO_RC2_WPU                  WPUCbits.WPUC2
#define IO_RC2_OD                   ODCONCbits.ODCC2
#define IO_RC2_ANS                  ANSELCbits.ANSC2
#define IO_RC2_SetHigh()            do { LATCbits.LATC2 = 1; } while(0)
#define IO_RC2_SetLow()             do { LATCbits.LATC2 = 0; } while(0)
#define IO_RC2_Toggle()             do { LATCbits.LATC2 = ~LATCbits.LATC2; } while(0)
#define IO_RC2_GetValue()           PORTCbits.RC2
#define IO_RC2_SetDigitalInput()    do { TRISCbits.TRISC2 = 1; } while(0)
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
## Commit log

2025-02-16 Added 6502 emulator submodule
2025-02-16 Working use of 6502 emulation library
2025-02-17 Added memory map
2025-02-22 Init software boilerplate and Makefile
2025-02-22 Fixed bug in makefile
2025-02-22 Working vm and cc65 config
2025-02-22 Working hello world
2025-02-22 readme add "implemented so far"
2025-03-01 Created KiCad project
2025-03-01 Updated docs
2025-03-01 Remove KiCad lock file; do not track
2025-05-23 Beginning of addr decode with mux
2025-06-08 KiCAD schematic is mostly complete
2025-06-08 Preliminary schematic
2025-06-15 Schematic is nearly done
2025-06-15 Most footprints assigned
2025-06-16 Ready to begin pcb layout
2025-06-17 Overhaul of structure, etc
2025-06-19 Some connector changes
2025-06-19 Made DMA peripheral stuff on same board
2025-06-19 footprint assignments and separate project for RAM board
2025-06-25 Peripheral io layout done; snapshot of current state before redoing much of the rest of the layout.
2025-06-29 Layout mostly finished
2025-06-29 Fixed typo in KiCAD project name
2025-07-04 Layout of Rev a is finished
2025-07-04 Generated Gerbers
2025-07-04 Plotted schematic
2025-07-04 Added hardware specification
2025-07-04 Implementation plan
2025-07-05 Initial kernel project setup
2025-07-05 Created MPLAB project
2025-07-05 linguist ignore kicad html bom
2025-07-05 Added some PIC build files to gitignore
2025-07-05 Moved MPLAB project directory
2025-07-05 MPLAB project config
2025-07-06 MCC generated code
2025-07-06 Added pcb renders
2025-07-13 Initial PIC hardware control code
2025-07-13 Beginnings of the debug bootloading scheme
2025-07-13 u6loader.py
2025-07-17 Blinky light on the PIC is working!!!
2025-07-17 Add ability to release PIC reset from makefile target
2025-07-17 PIC hello world is working
2025-07-17 basic uart is working
2025-07-20 Some kernel design ideas
2025-07-24 EEPROM IS WORKING!!!!!
2025-07-24 Better pic debug shell
2025-10-11 Commit to save current state. SRAM access not working, figured out some latching issues
2025-10-11 Single-byte writes might be working
2025-10-11 Single-byte SRAM reads/writes work after changing a jumper
2025-10-11 Improved shell
2025-10-11 Made shell 115200 baud
2025-10-11 Update PIC to Dual-port SRAM communication status
2025-10-11 Python PIC Bridge library working
2025-10-18 working blinking on 6502
2025-10-26 Working dma_access blinky 6502 program
2025-10-26 Restructured loader tests
2025-10-26 Tested memory write
2025-10-26 Added image of current PCB for README
2025-10-26 Rename reworded_board.jpg to reworked_board.jpg
2025-10-26 Revise PCB status and add images
    Updated the current status of the PCB assembly and functionality.
